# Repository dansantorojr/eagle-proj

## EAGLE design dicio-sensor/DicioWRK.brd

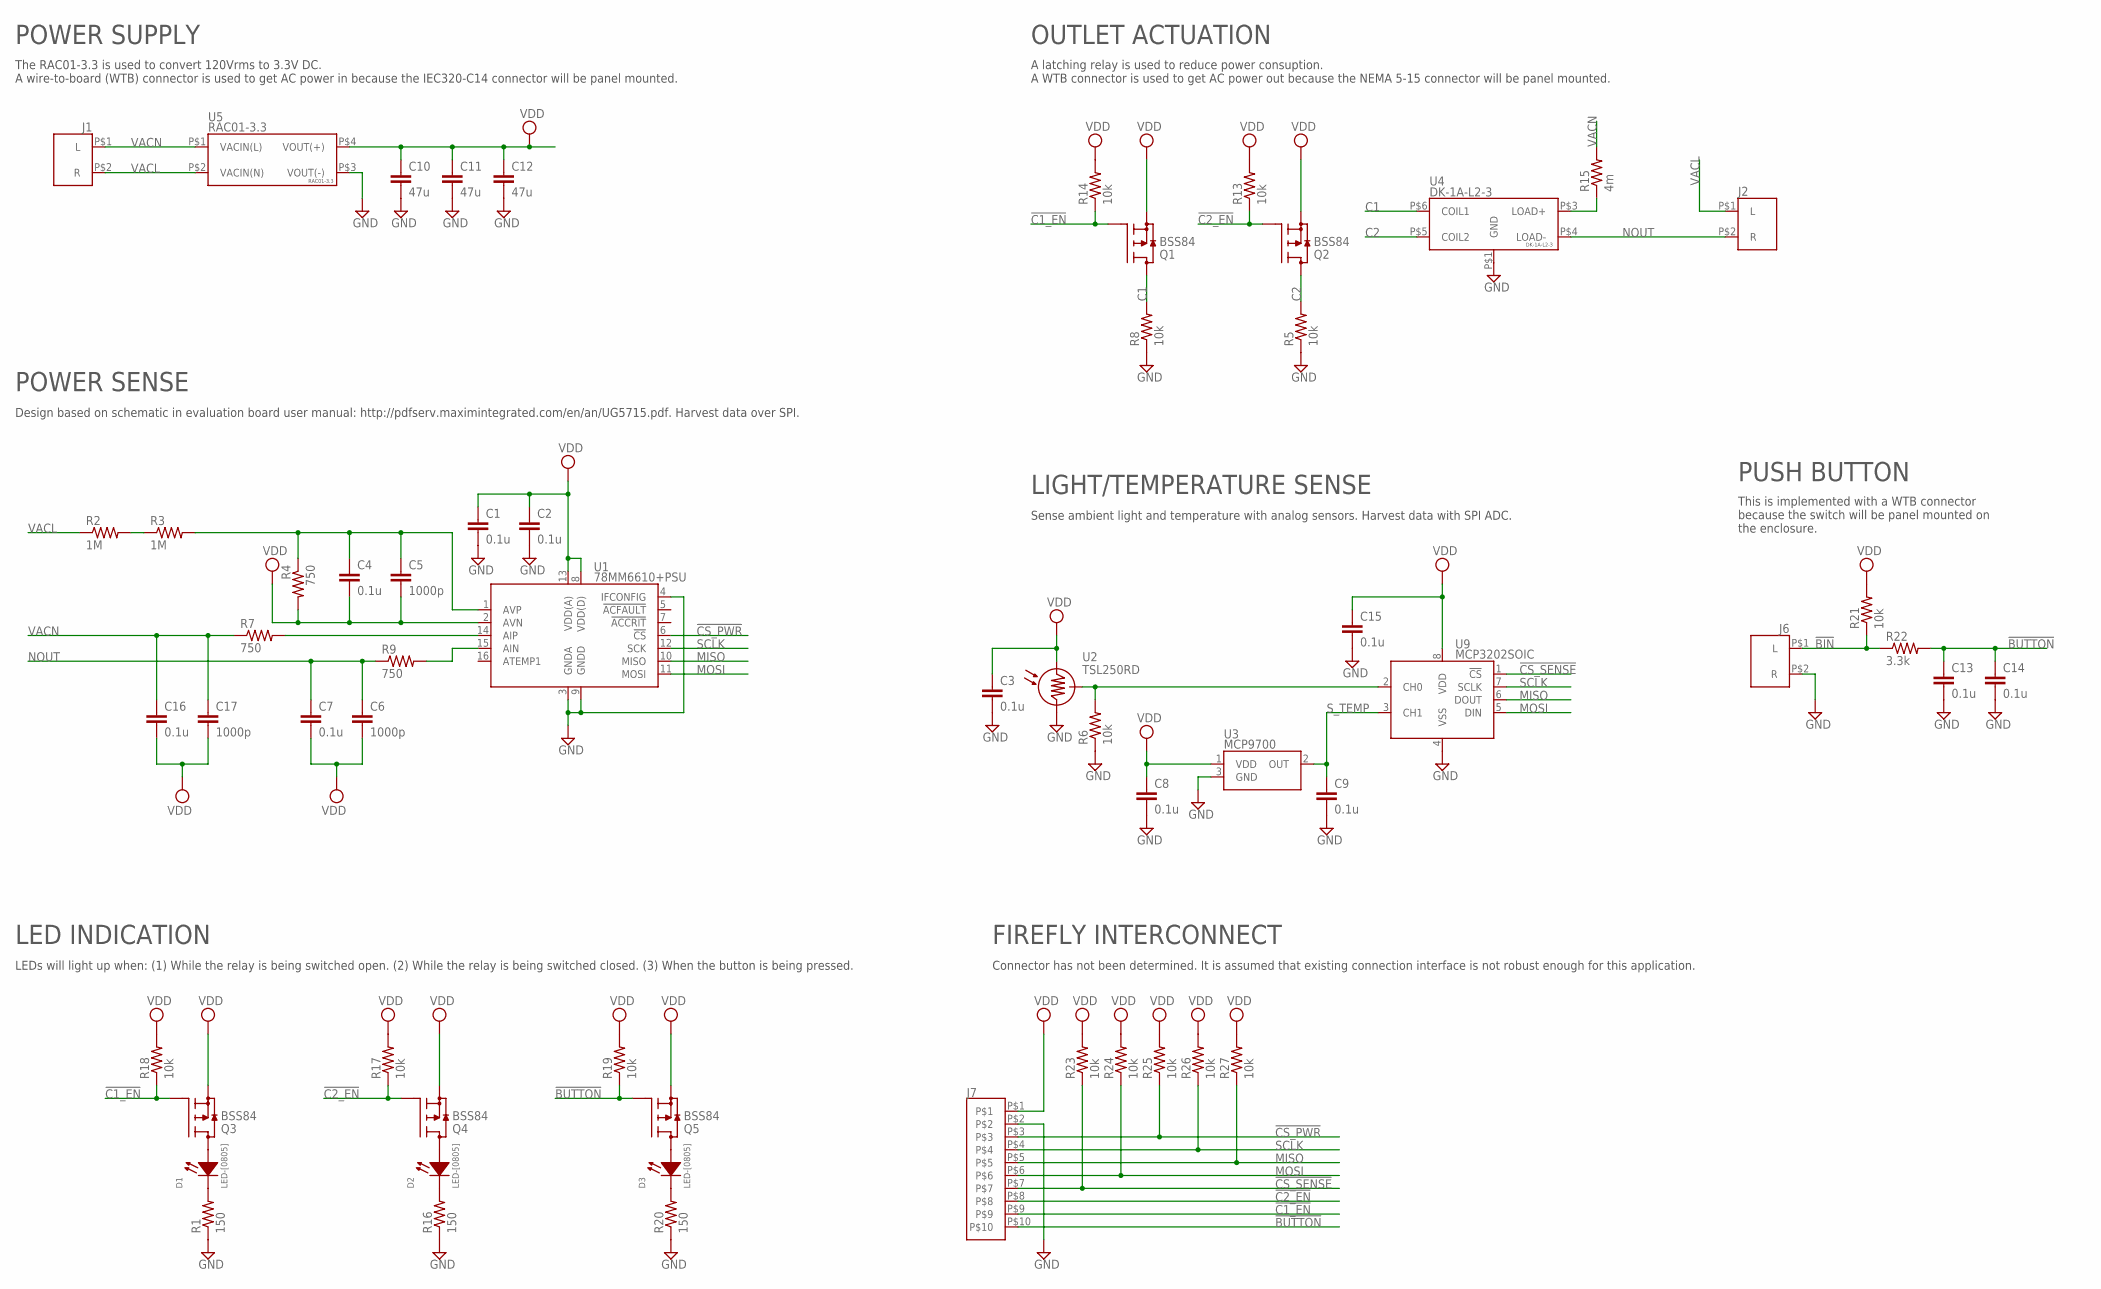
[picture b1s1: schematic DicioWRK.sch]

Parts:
C1, C2, C3, C4, C7, C8, C9, C13, C14, C15, C16: 0.1u; C0805
C5, C6, C17: 1000p; C0805
C10, C11, C12: 47u; C1206
D1, D2, D3: LED-[0805]; L0805
J1, J2, J6: WTB-2; [TERM][2][0.2]
J7: TERM10
Q1, Q2, Q3, Q4, Q5: BSS84; SOT23
R1, R16, R20: 150; R0805
R2, R3: 1M; R0805
R4, R7, R9: 750; R0805
R5, R6, R8, R13, R14, R17, R18, R19, R21, R23, R24, R25, R26, R27: 10k; R0805
R15: 4m; R2512
R22: 3.3k; R0805
U1: 78MM6610+PSU; TSSOP16
U2: TSL250RD; SOIC8
U3: MCP9700; SOT23
U4: DK-1A-L2-3
U5: RAC01-3.3
U9: MCP3202SOIC; SOIC8

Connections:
!BIN!: J6.P$1 (L), R21.1, R22.1
!BUTTON!: C13.1, C14.1, J7.P$10, Q5.1 (G), R19.1, R22.2
!C1_EN!: J7.P$9, Q1.1 (G), Q3.1 (G), R14.1, R18.1
!C2_EN!: J7.P$8, Q2.1 (G), Q4.1 (G), R13.1, R17.1
!CS_PWR!: J7.P$3, R25.1, U1.6 (!CS!)
!CS_SENSE!: J7.P$7, R23.1, U9.1 (!CS!)
C1: Q1.3 (D), R8.2, U4.P$6 (COIL1)
C2: Q2.3 (D), R5.2, U4.P$5 (COIL2)
GND: C1.2, C2.2, C3.2, C8.2, C9.2, C10.2, C11.2, C12.2, C13.2, C14.2, C15.2, J6.P$2 (R), J7.P$2, R1.1, R5.1, R6.1, R8.1, R16.1, R20.1, U1.3 (GNDA), U1.4 (IFCONFIG), U1.9 (GNDD), U2.4 (GND), U3.3 (GND), U4.P$1 (GND), U5.P$3 (VOUT(-)), U9.4 (VSS)
MISO: J7.P$5, R27.1, U1.10 (MISO), U9.6 (DOUT)
MOSI: J7.P$6, R24.1, U1.11 (MOSI), U9.5 (DIN)
unnamed: C4.1, C5.1, R3.2, R4.1, U1.1 (AVP)
unnamed: R2.2, R3.1
unnamed: D2.1 (A), Q4.3 (D)
unnamed: R6.2, U2.7 (OUT), U9.2 (CH0)
unnamed: D1.1 (A), Q3.3 (D)
unnamed: R15.1, U4.P$3 (LOAD+)
unnamed: D1.2 (C), R1.2
unnamed: D2.2 (C), R16.2
unnamed: D3.1 (A), Q5.3 (D)
unnamed: D3.2 (C), R20.2
unnamed: R7.2, U1.14 (AIP)
unnamed: R9.2, U1.15 (AIN)
NOUT: C6.1, C7.1, J2.P$2 (R), R9.1, U4.P$4 (LOAD-)
SCLK: J7.P$4, R26.1, U1.12 (SCK), U9.7 (SCLK)
S_TEMP: C9.1, U3.2 (OUT), U9.3 (CH1)
VACL: J1.P$2 (R), J2.P$1 (L), R2.1, U5.P$2 (VACIN(N))
VACN: C16.1, C17.1, J1.P$1 (L), R7.1, R15.2, U5.P$1 (VACIN(L))
VDD: C1.1, C2.1, C3.1, C4.2, C5.2, C6.2, C7.2, C8.1, C10.1, C11.1, C12.1, C15.1, C16.2, C17.2, J7.P$1, Q1.2 (S), Q2.2 (S), Q3.2 (S), Q4.2 (S), Q5.2 (S), R4.2, R13.2, R14.2, R17.2, R18.2, R19.2, R21.2, R23.2, R24.2, R25.2, R26.2, R27.2, U1.2 (AVN), U1.8 (VDD(D)), U1.13 (VDD(A)), U2.6 (VDD), U3.1 (VDD), U5.P$4 (VOUT(+)), U9.8 (VDD)

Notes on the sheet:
POWER SUPPLY
OUTLET ACTUATION
POWER SENSE
LIGHT/TEMPERATURE SENSE
LED INDICATION
Design based on schematic in evaluation board user manual: http://pdfserv.maximintegrated.com/en/an/UG5715.pdf. Harvest data over SPI.
The RAC01-3.3 is used to convert 120Vrms to 3.3V DC. A wire-to-board (WTB) connector is used to get AC power in because the IEC320-C14 connector will be panel mounted.
LEDs will light up when: (1) While the relay is being switched open. (2) While the relay is being switched closed. (3) When the button is being pressed.
A latching relay is used to reduce power consuption. A WTB connector is used to get AC power out because the NEMA 5-15 connector will be panel mounted.
Sense ambient light and temperature with analog sensors. Harvest data with SPI ADC.
PUSH BUTTON
This is implemented with a WTB connector because the switch will be panel mounted on the enclosure.
FIREFLY INTERCONNECT
Connector has not been determined. It is assumed that existing connection interface is not robust enough for this application.

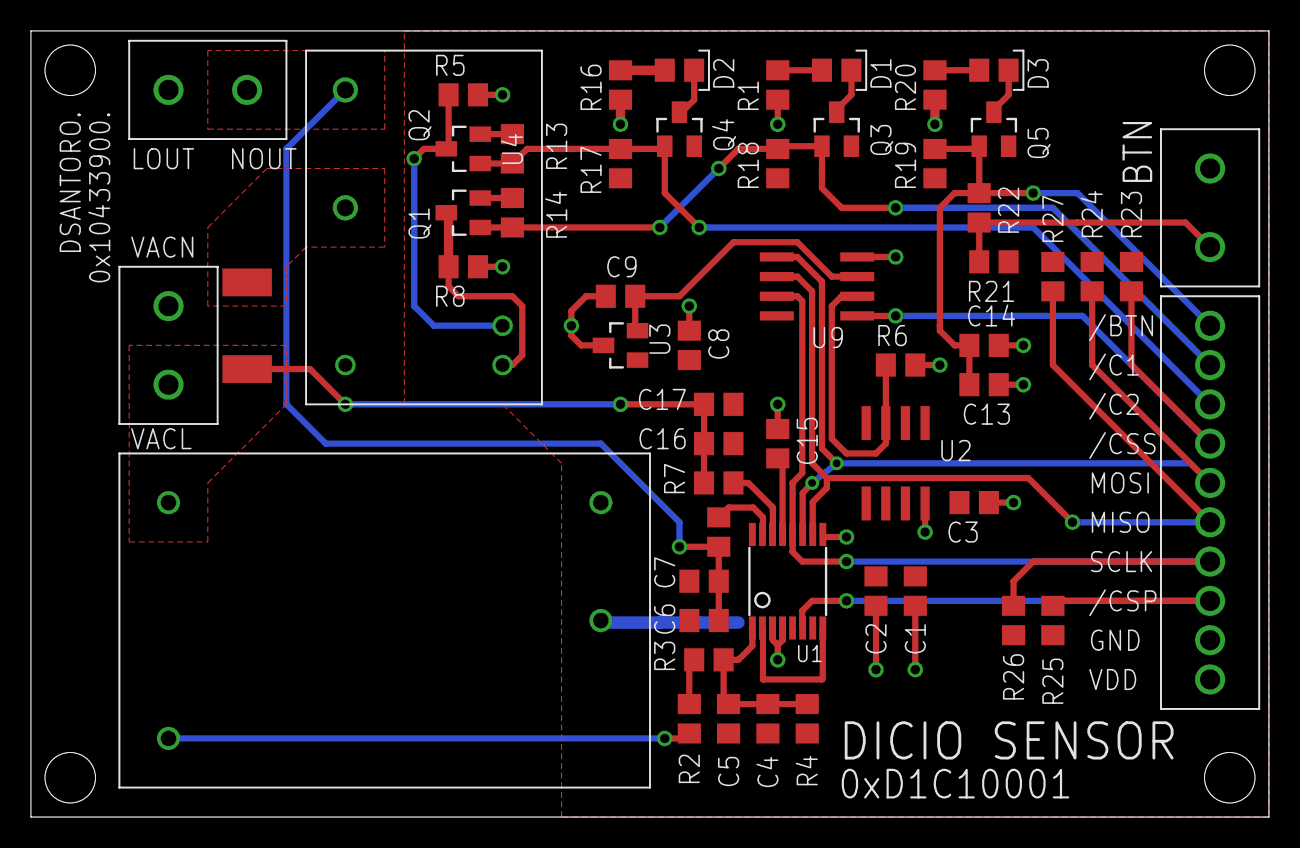
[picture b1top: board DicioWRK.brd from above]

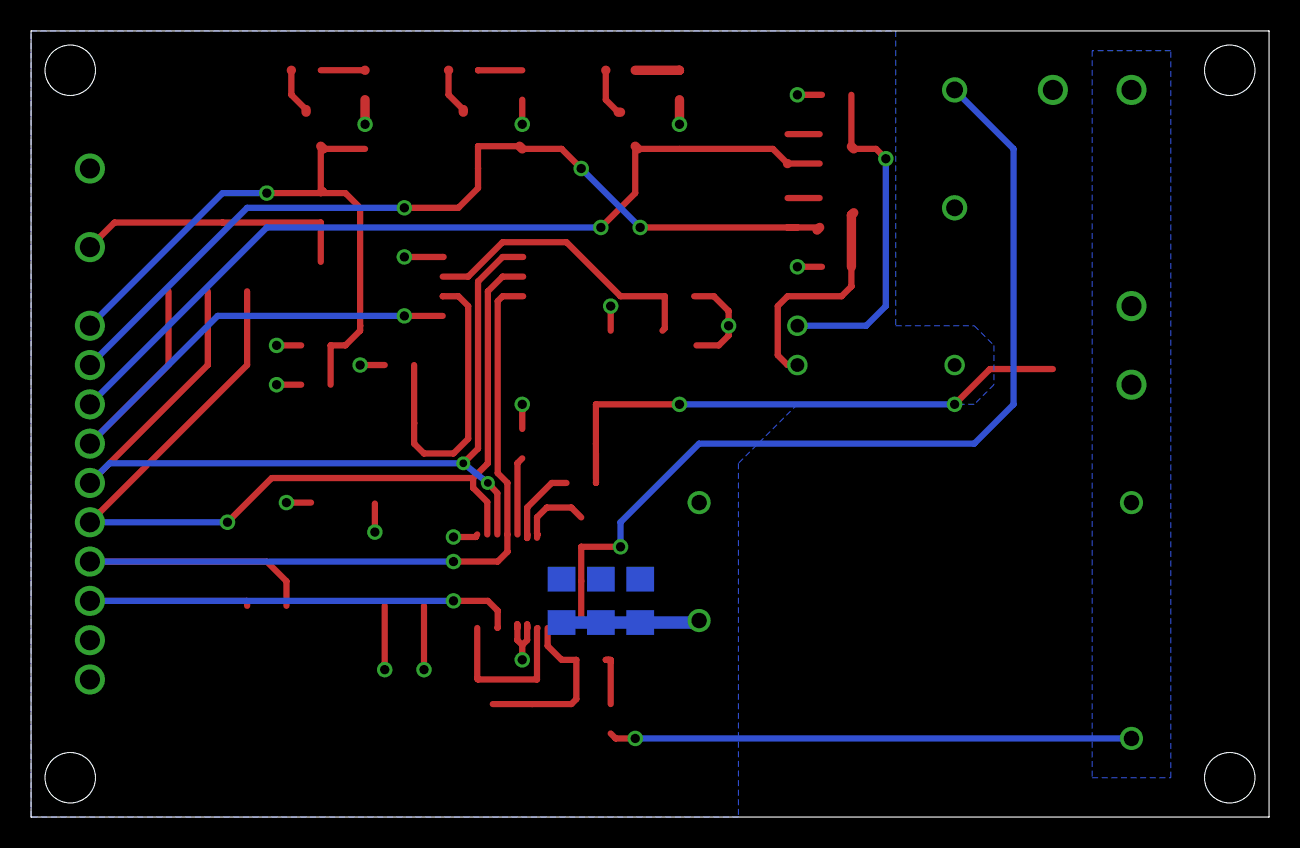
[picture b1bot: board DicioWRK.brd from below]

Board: 2 copper layers, 80.0 x 50.8 mm, 59 parts (3 on the bottom side), 29 nets.

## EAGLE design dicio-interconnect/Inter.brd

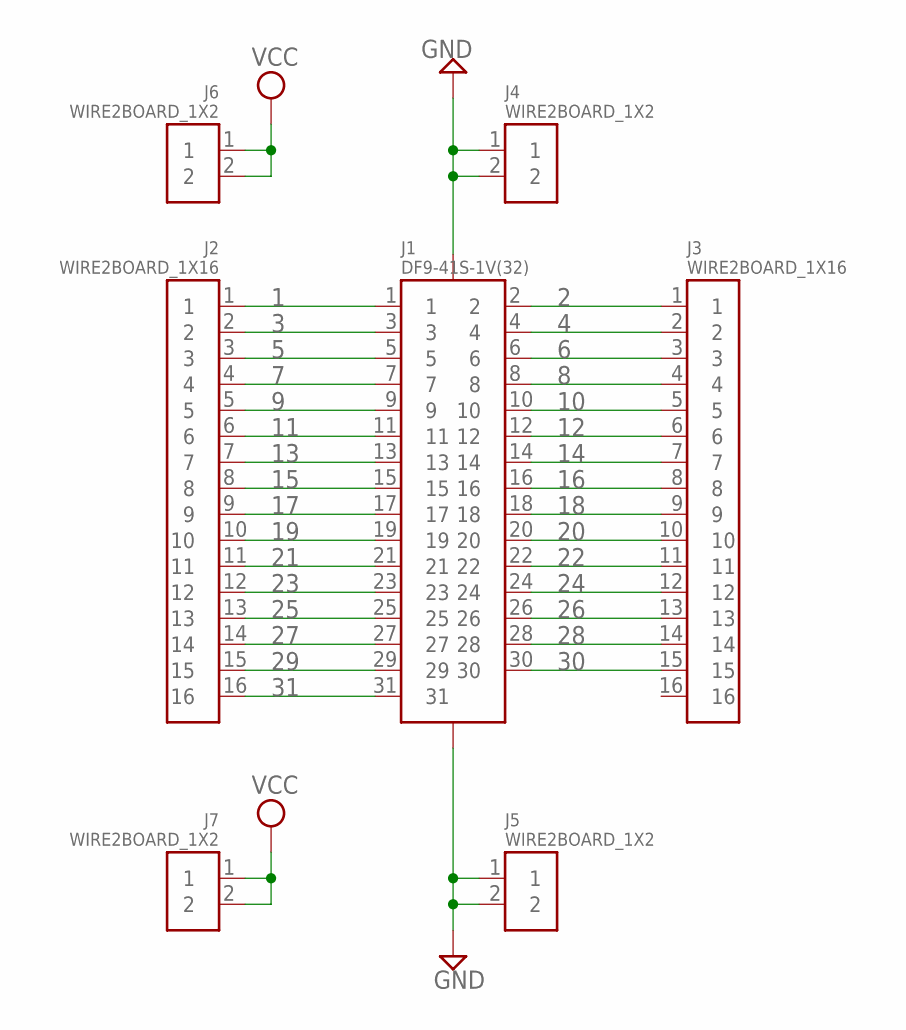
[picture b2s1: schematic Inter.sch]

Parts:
J1: DF9-41S-1V(32)
J2, J3: WIRE2BOARD_1X16
J4, J5, J6, J7: WIRE2BOARD_1X2

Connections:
1: J1.1, J2.1
2: J1.2, J3.1
3: J1.3, J2.2
4: J1.4, J3.2
5: J1.5, J2.3
6: J1.6, J3.3
7: J1.7, J2.4
8: J1.8, J3.4
9: J1.9, J2.5
10: J1.10, J3.5
11: J1.11, J2.6
12: J1.12, J3.6
13: J1.13, J2.7
14: J1.14, J3.7
15: J1.15, J2.8
16: J1.16, J3.8
17: J1.17, J2.9
18: J1.18, J3.9
19: J1.19, J2.10
20: J1.20, J3.10
21: J1.21, J2.11
22: J1.22, J3.11
23: J1.23, J2.12
24: J1.24, J3.12
25: J1.25, J2.13
26: J1.26, J3.13
27: J1.27, J2.14
28: J1.28, J3.14
29: J1.29, J2.15
30: J1.30, J3.15
31: J1.31, J2.16
GND: J1.32, J1.33, J4.1, J4.2, J5.1, J5.2
VCC: J6.1, J6.2, J7.1, J7.2

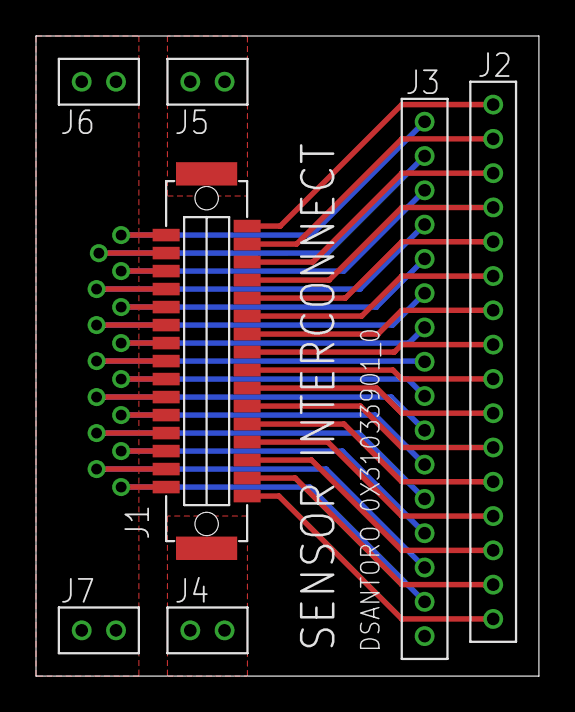
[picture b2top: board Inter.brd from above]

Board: 2 copper layers, 27.9 x 35.6 mm, 7 parts (0 on the bottom side), 33 nets.

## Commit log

2016-04-03 Working on Rev. 2.
2016-04-04 Dicio sensor Rev 1
2016-04-05 R1-Out for Fab.
2016-04-05 add zip
2016-06-29 No updates.
